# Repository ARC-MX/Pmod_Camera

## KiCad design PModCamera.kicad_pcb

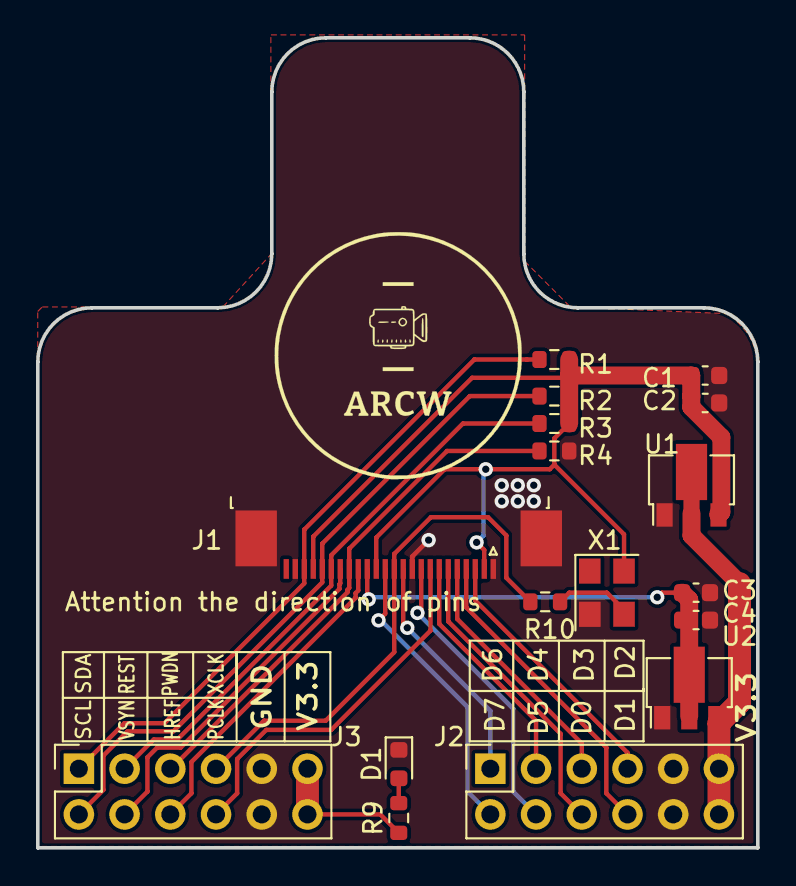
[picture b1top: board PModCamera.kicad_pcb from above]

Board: 2 copper layers, 40.0 x 45.0 mm, 17 parts (0 on the bottom side), 22 nets.

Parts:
C1, C2, C3, C4: 104; C_0603_1608Metric
D1: TSAL4400; LED_0603_1608Metric
J1: Conn_01x24_MountingPin; TE_2-1734839-4_1x24-1MP_P0.5mm_Horizontal
J2, J3: Conn_02x06_Odd_Even; PinSocket_2x06_P2.54mm_Vertical
R1, R2, R3, R4: 3.9K; R_0603_1608Metric
R9: 500R; R_0603_1608Metric
R10: 100R; R_0603_1608Metric
U1: AMS1117-2.85; SOT-89-3
U2: AMS1117-1.5; SOT-89-3
X1: SG-5032CAN; Oscillator_SMD_SeikoEpson_SG8002CE-4Pin_3.2x2.5mm

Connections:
+1V5: C3.1, C4.1, J1.15, U2.2
+2V8: C1.1, C2.1, J1.2, J1.14, J1.21, R1.1, R2.1, R3.1, U1.3, X1.4
+3V3: J2.11, J2.12, J3.11, J3.12, R9.1, U1.2, U2.3
/OV1_D0: J1.6, J2.6
/OV1_D1: J1.4, J2.8
/OV1_D2: J1.3, J2.7
/OV1_D3: J1.5, J2.5
/OV1_D4: J1.7, J2.3
/OV1_D5: J1.9, J2.4
/OV1_D6: J1.11, J2.1
/OV1_D7: J1.13, J2.2
/OV1_HREF: J1.16, J3.6
/OV1_PCLK: J1.8, J3.8
/OV1_PWDN: J1.17, J3.5, R4.1
/OV1_RESET: J1.19, J3.3, R3.2
/OV1_SCL: J1.20, J3.2, R2.2
/OV1_SDA: J1.22, J3.1, R1.2
/OV1_VSYNC: J1.18, J3.4
/OV1_XCLK: J1.12, J3.7, R10.1
GND: C1.2, C2.2, C3.2, C4.2, D1.1, J1.1, J1.10, J1.23, J1.MP, J2.9, J2.10, J3.9, J3.10, R4.2, U1.1, U2.1, X1.2
unnamed: D1.2, R9.2
unnamed: R10.2, X1.3

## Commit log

2021-03-12 修改等长线
